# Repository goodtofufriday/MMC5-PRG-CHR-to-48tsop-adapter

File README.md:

*BOARDS NEED TO HAVE GROUND PLANE ADDED TO THEM FOR STABILITY! They work but after even a few minutes crash, consensus is due to lack of ground plane. Will update when i have time.*

THIS IS NOW IN TESTING! Only the piggyback version has been updated to include a ground plane and larger bridging pads.

This project is for the NES / Famicom to be able to use flash chips for translations or replace dead roms. Also sram.

Everything created in eagle. Feel free to use with credit.

Piggyback version included. You need to pull chip enable and connect to 5v to disable the rom.

MMC5 / PRG / CHR to 48TSOP Flash Adatper

Replace roms with this board. Use 5v 8megabit flash

Below are instructions for the multi-board adapter. You can use this even for 28 pin rom boards.

Place on back of rom. Pull rom CE/OE + pull high 

Bridge Pin1 and 3 for all EXCEPT 128kb chr or Nrom boards

MMC5: Bridge all six circled jumpers

CHR: Bridge 3rd Circle + 1st square for 256kb

PRG: Bridge 1st Circle + 2nd square for 512kb or Top pads for 256kb

Also included is a ram adapter for romhacks like megaman minus inifinity. use ram IS61C256AL

Oshpark links: 

Piggyback ver. https://oshpark.com/shared_projects/Uz4v9Vq7

Ram adapter https://oshpark.com/shared_projects/bVWn1u0x

MMC5 only ver. https://oshpark.com/shared_projects/fcmApdiZ

Special thanks to https://github.com/techav-homebrew/LCC32-DIP32-Flash-Adapter for saving me some time on the 32pin board. Everything else is custom, hence the included libraries.

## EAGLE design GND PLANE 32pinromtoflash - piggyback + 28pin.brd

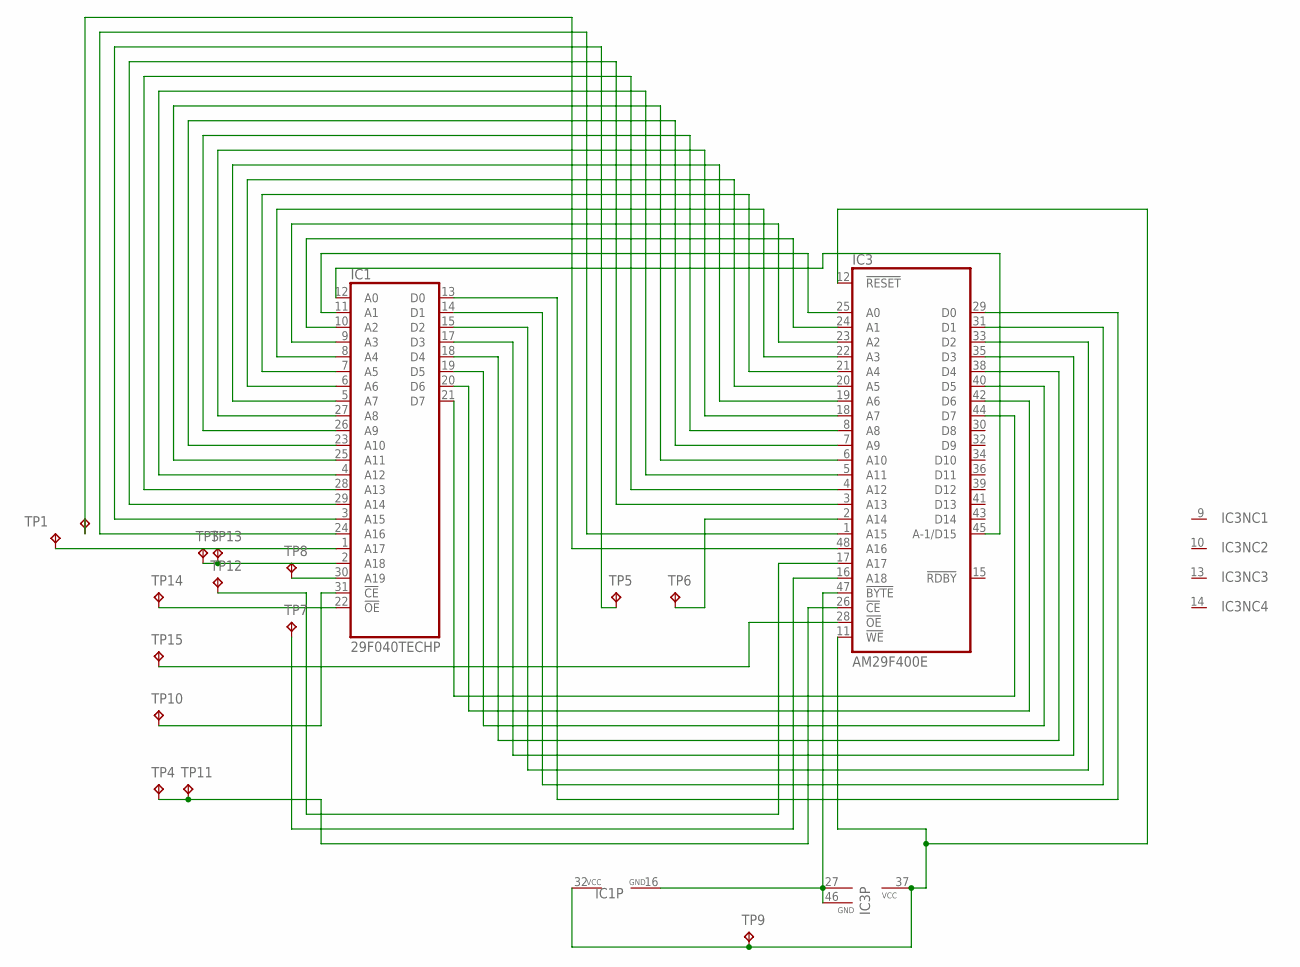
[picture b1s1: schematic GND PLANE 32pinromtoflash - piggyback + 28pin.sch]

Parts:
IC1: 29F040TECHP; DIL32-3
IC3: AM29F400E; TSOP48
TP1, TP2, TP3, TP4, TP5, TP6, TP7, TP8, TP9, TP10, TP11, TP12, TP13, TP14, TP15: TPTP15SQ; TP15SQ

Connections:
A14FLASH: IC3.2 (A14), TP6.TP
A17FLASH: IC3.17 (A17), TP12.TP
A17PIN1ROM: IC1.1 (A17), TP1.TP
A18FLASH: IC3.48 (A16), TP2.TP
CEFLASH: IC3.26 (!CE), TP4.TP, TP11.TP
CEROMPIN31: IC1.31 (!CE), TP10.TP
FLASH-A18: IC3.16 (A18), TP7.TP
MMC5-A0: IC1.12 (A0), IC3.45 (A-1/D15)
MMC5-A1: IC1.11 (A1), IC3.25 (A0)
MMC5-A2: IC1.10 (A2), IC3.24 (A1)
MMC5-A3: IC1.9 (A3), IC3.23 (A2)
MMC5-A4: IC1.8 (A4), IC3.22 (A3)
MMC5-A5: IC1.7 (A5), IC3.21 (A4)
MMC5-A6: IC1.6 (A6), IC3.20 (A5)
MMC5-A7: IC1.5 (A7), IC3.19 (A6)
MMC5-A8: IC1.27 (A8), IC3.18 (A7)
MMC5-A9: IC1.26 (A9), IC3.8 (A8)
MMC5-A10: IC1.23 (A10), IC3.7 (A9)
MMC5-A11: IC1.25 (A11), IC3.6 (A10)
MMC5-A12: IC1.4 (A12), IC3.5 (A11)
MMC5-A13: IC1.28 (A13), IC3.4 (A12)
MMC5-A14: IC1.29 (A14), IC3.3 (A13)
MMC5-A15: IC1.3 (A15), TP5.TP
MMC5-A16: IC1.24 (A16), IC3.1 (A15)
MMC5-A19: IC1.30 (A19), TP8.TP
MMC5-D0: IC1.13 (D0), IC3.29 (D0)
MMC5-D1: IC1.14 (D1), IC3.31 (D1)
MMC5-D2: IC1.15 (D2), IC3.33 (D2)
MMC5-D3: IC1.17 (D3), IC3.35 (D3)
MMC5-D4: IC1.18 (D4), IC3.38 (D4)
MMC5-D5: IC1.19 (D5), IC3.40 (D5)
MMC5-D6: IC1.20 (D6), IC3.42 (D6)
MMC5-D7: IC1.21 (D7), IC3.44 (D7)
MMC5-VCC: IC1.32 (VCC), IC3.11 (!WE), IC3.12 (!RESET), IC3.37 (VCC), TP9.TP
MMC5-VSS: IC1.16 (GND), IC3.27 (GND), IC3.46 (GND), IC3.47 (!BYTE)
OEFLASH: IC3.28 (!OE), TP15.TP
PIN2ROM: IC1.2 (A18), TP3.TP, TP13.TP
PIN22ROM: IC1.22 (!OE), TP14.TP

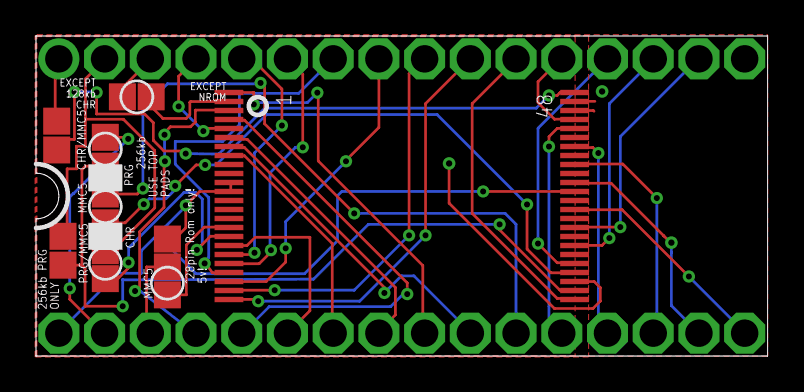
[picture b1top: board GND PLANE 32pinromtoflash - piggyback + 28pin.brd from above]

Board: 2 copper layers, 40.6 x 17.8 mm, 17 parts (1 on the bottom side), 38 nets.

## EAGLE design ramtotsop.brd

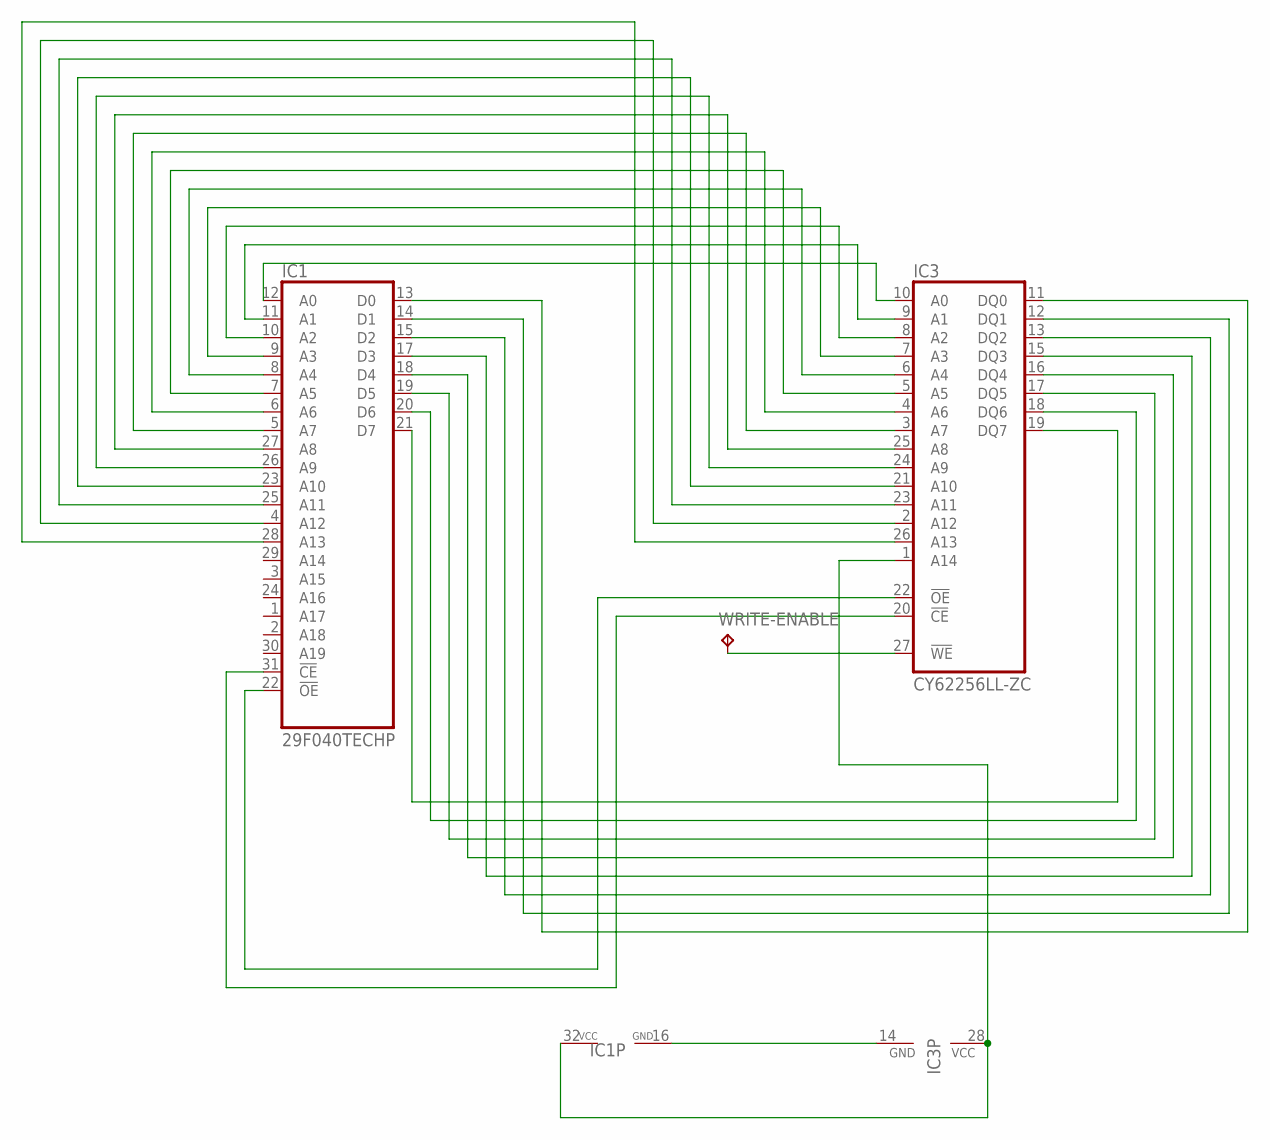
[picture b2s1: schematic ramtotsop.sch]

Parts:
IC1: 29F040TECHP; DIL32-3
IC3: CY62256LL-ZC; TSOP1-28
WRITE-ENABLE: TPTP20SQ; TP20SQ

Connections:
CEROMPIN31: IC1.31 (!CE), IC3.20 (!CE)
MMC5-A0: IC1.12 (A0), IC3.10 (A0)
MMC5-A1: IC1.11 (A1), IC3.9 (A1)
MMC5-A2: IC1.10 (A2), IC3.8 (A2)
MMC5-A3: IC1.9 (A3), IC3.7 (A3)
MMC5-A4: IC1.8 (A4), IC3.6 (A4)
MMC5-A5: IC1.7 (A5), IC3.5 (A5)
MMC5-A6: IC1.6 (A6), IC3.4 (A6)
MMC5-A7: IC1.5 (A7), IC3.3 (A7)
MMC5-A8: IC1.27 (A8), IC3.25 (A8)
MMC5-A9: IC1.26 (A9), IC3.24 (A9)
MMC5-A10: IC1.23 (A10), IC3.21 (A10)
MMC5-A11: IC1.25 (A11), IC3.23 (A11)
MMC5-A12: IC1.4 (A12), IC3.2 (A12)
MMC5-A13: IC1.28 (A13), IC3.26 (A13)
MMC5-D0: IC1.13 (D0), IC3.11 (DQ0)
MMC5-D1: IC1.14 (D1), IC3.12 (DQ1)
MMC5-D2: IC1.15 (D2), IC3.13 (DQ2)
MMC5-D3: IC1.17 (D3), IC3.15 (DQ3)
MMC5-D4: IC1.18 (D4), IC3.16 (DQ4)
MMC5-D5: IC1.19 (D5), IC3.17 (DQ5)
MMC5-D6: IC1.20 (D6), IC3.18 (DQ6)
MMC5-D7: IC1.21 (D7), IC3.19 (DQ7)
MMC5-VCC: IC1.32 (VCC), IC3.1 (A14), IC3.28 (VCC)
MMC5-VSS: IC1.16 (GND), IC3.14 (GND)
unnamed: IC1.22 (!OE), IC3.22 (!OE)
WRITE-ENABLE: IC3.27 (!WE), WRITE-ENABLE.TP

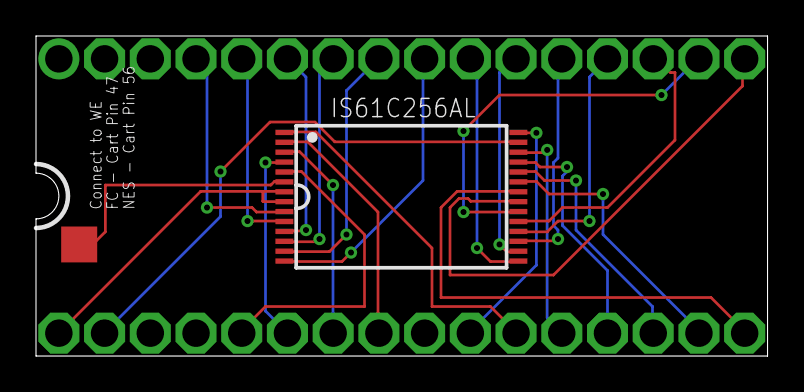
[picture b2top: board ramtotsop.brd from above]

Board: 2 copper layers, 40.6 x 17.8 mm, 3 parts (1 on the bottom side), 27 nets.

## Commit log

2025-02-19 Intro.md
2025-02-19 Rename c07aa391b73b8d821541fbc97d9f78d4.png to front.png
2025-02-19 Rename f20dbbbddf84e133c33a3f7c54fae38b.png to back.png
